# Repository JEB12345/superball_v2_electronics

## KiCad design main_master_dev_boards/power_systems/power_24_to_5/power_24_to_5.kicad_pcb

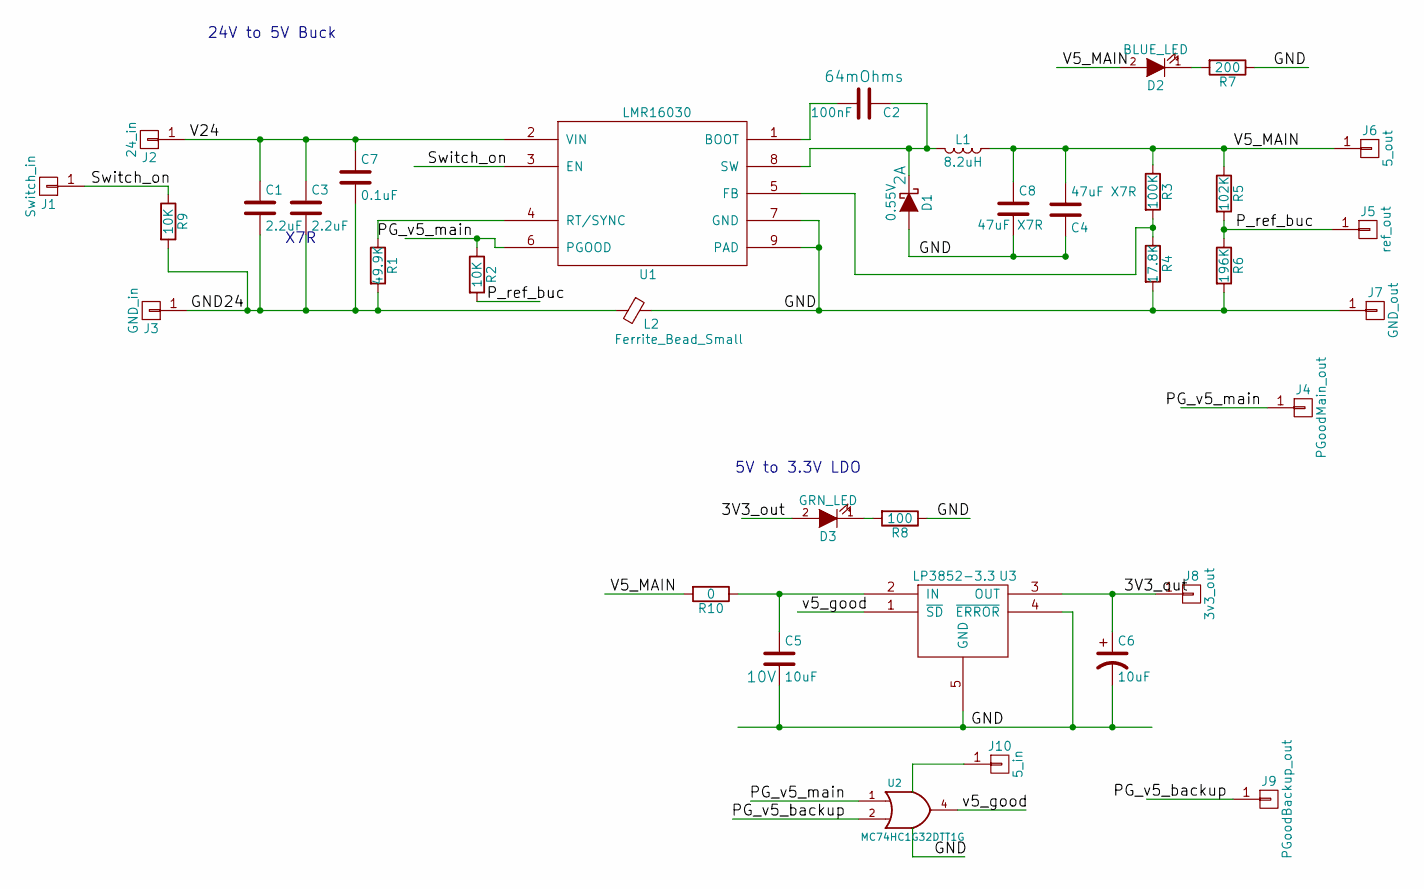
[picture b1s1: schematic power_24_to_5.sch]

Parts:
C1, C3: 2.2uF; C_0805_HandSoldering
C2: 100nF; C_0805_HandSoldering
C4, C8: 47uF X7R; C_2220_HandSoldering
C5: 10uF; C_0805_HandSoldering; Voltage 10V
C6: 10uF; C_0805_HandSoldering
C7: 0.1uF; C_0805_HandSoldering
D1: 0.55V; D_SOD-123
D2: BLUE_LED; LED_0603
D3: GRN_LED; LED_0603
J1: Switch_in; pinhead-01x01_3x1
J2: 24_in; pinhead-01x01_3x1
J3: GND_in; pinhead-01x01_3x1_square
J4: PGoodMain_out; pinhead-01x01_3x1
J5: ref_out; pinhead-01x01_3x1
J6: 5_out; pinhead-01x01_3x1
J7: GND_out; pinhead-01x01_3x1_square
J8: 3v3_out; pinhead-01x01_3x1
J9: PGoodBackup_out; pinhead-01x01_3x1
J10: 5_in; pinhead-01x01_3x1
L1: 8.2uH; Bourns-SRP7028A
L2: Ferrite_Bead_Small; C_0805_HandSoldering
R1: 49.9K; R_0805_HandSoldering
R2, R9: 10K; R_0805_HandSoldering
R3: 100K; R_0805_HandSoldering
R4: 17.8K; R_0805_HandSoldering
R5: 102K; R_0805_HandSoldering
R6: 196K; R_0805_HandSoldering
R7: 200; R_0805_HandSoldering
R8: 100; R_0805_HandSoldering
R10: 0; R_0603
U1: LMR16030; HSOIC-8-1EP_Pitch1.27mm_noVias
U2: MC74HC1G32DTT1G; SOT-23-5_HandSoldering
U3: LP3852-3.3; SOT-223

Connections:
/3V3_out: C6.1, D3.2 (A), J8.1, U3.3 (OUT)
/GND24: C1.2, C3.2, C7.2, J3.1, L2.2, R1.2, R9.2
/PG_v5_backup: J9.1, U2.2
/PG_v5_main: J4.1, R2.1, U1.6 (PGOOD), U2.1
/P_ref_buc: J5.1, R2.2, R5.2, R6.1
/Switch_on: J1.1, R9.1, U1.3 (EN)
/V5_MAIN: C4.2, C8.1, D2.2 (A), J6.1, L1.1, R3.1, R5.1, R10.2
/V24: C1.1, C3.1, C7.1, J2.1, U1.2 (VIN)
/v5_good: U2.4, U3.1 (~SD)
GND: C4.1, C5.2, C6.2, C8.2, D1.2 (A), J7.1, L2.1, R4.2, R6.2, R7.1, R8.1, U1.7 (GND), U1.9 (PAD), U2.3 (GND), U3.4 (~ERROR), U3.5 (GND)
unnamed: C2.1, D1.1 (K), L1.2, U1.8 (SW)
unnamed: C2.2, U1.1 (BOOT)
unnamed: C5.1, R10.1, U3.2 (IN)
unnamed: D2.1 (K), R7.2
unnamed: D3.1 (K), R8.2
unnamed: R1.1, U1.4 (RT/SYNC)
unnamed: R3.2, R4.1, U1.5 (FB)
VCC: J10.1, U2.5 (VCC)

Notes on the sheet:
24V to 5V Buck
5V to 3.3V LDO
X7R

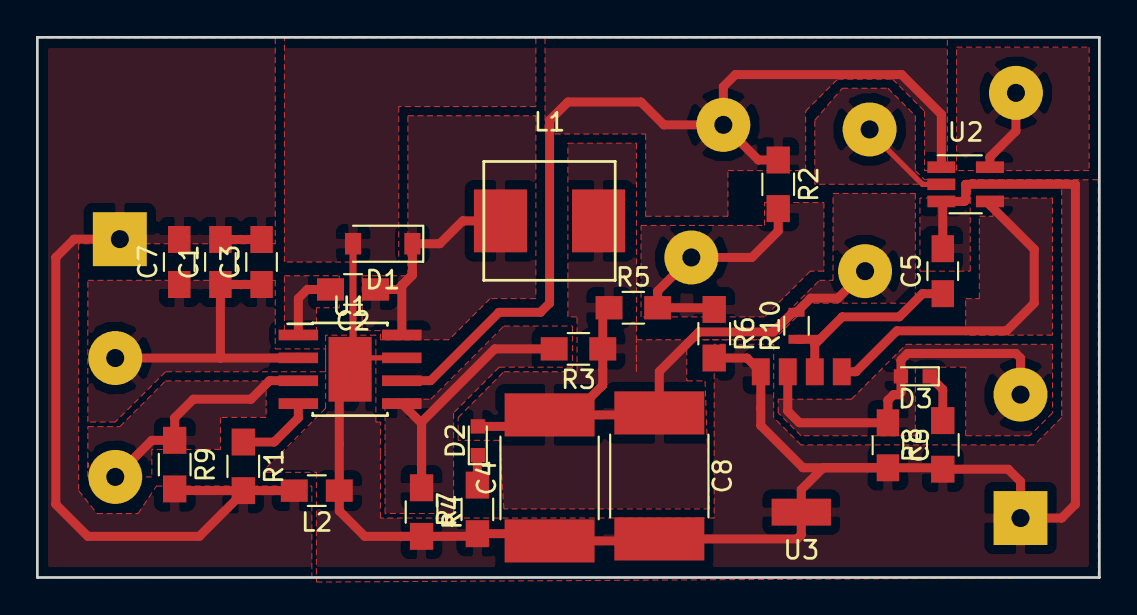
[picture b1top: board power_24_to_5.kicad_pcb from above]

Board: 2 copper layers, 59.0 x 30.0 mm, 36 parts (0 on the bottom side), 18 nets.

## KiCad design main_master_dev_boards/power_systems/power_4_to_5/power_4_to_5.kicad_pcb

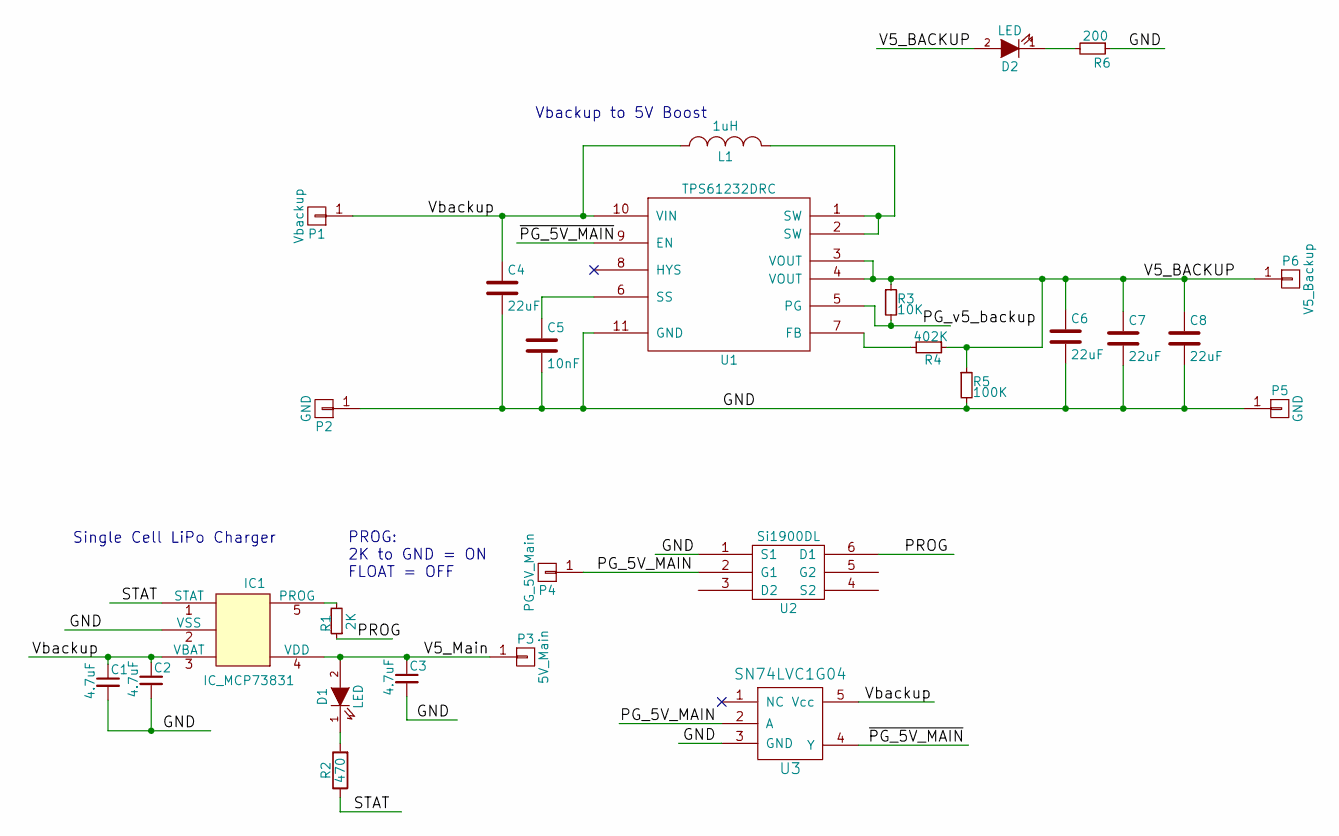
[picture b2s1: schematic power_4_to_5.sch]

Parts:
C1, C2, C3: 4.7uF; C_0805_HandSoldering
C4, C6, C7, C8: 22uF; C_0805_HandSoldering
C5: 10nF; C_0805_HandSoldering
D1, D2: LED; LED_0805
IC1: IC_MCP73831; dp_devices-SOT-23-5
L1: 1uH; XFL4020
P1: Vbackup; pinhead-01x01_3x1
P2, P5: GND; pinhead-01x01_3x1_square
P3: 5V_Main; pinhead-01x01_3x1
P4: PG_5V_Main; pinhead-01x01_3x1
P6: V5_Backup; pinhead-01x01_3x1
R1: 2K; R_0805_HandSoldering
R2: 470; R_0805_HandSoldering
R3: 10K; R_0805_HandSoldering
R4: 402K; R_0805_HandSoldering
R5: 100K; R_0805_HandSoldering
R6: 200; R_0805_HandSoldering
U1: TPS61232DRC; DFN-10-1EP_3x3mm_Pitch0.5mm
U2: Si1900DL; SOT323-6
U3: SN74LVC1G04; SOT-23-5_HandSoldering

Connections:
/GND: C1.2, C2.2, C3.2, C4.2, C5.2, C6.2, C7.2, C8.2, IC1.2 (VSS), P2.1, P5.1, R5.2, R6.1, U1.11 (GND), U2.1 (S1), U3.3 (GND)
/PG_5V_MAIN: P4.1, U2.2 (G1), U3.2 (A)
/PG_v5_backup: R3.2, U1.5 (PG)
/PROG: R1.1, U2.6 (D1)
/STAT: IC1.1 (STAT), R2.1
/V5_BACKUP: C6.1, C7.1, C8.1, D2.2 (A), P6.1, R3.1, R4.1, R5.1, U1.3 (VOUT), U1.4 (VOUT)
/V5_Main: C3.1, D1.2 (A), IC1.4 (VDD), P3.1
/Vbackup: C1.1, C2.1, C4.1, IC1.3 (VBAT), L1.1, P1.1, U1.10 (VIN), U3.5 (Vcc)
/~PG_5V_MAIN: U1.9 (EN), U3.4 (Y)
unnamed: C5.1, U1.6 (SS)
unnamed: D1.1 (K), R2.2
unnamed: D2.1 (K), R6.2
unnamed: IC1.5 (PROG), R1.2
unnamed: L1.2, U1.1 (SW), U1.2 (SW)
unnamed: R4.2, U1.7 (FB)

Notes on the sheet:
Single Cell LiPo Charger
Vbackup to 5V Boost
PROG: 2K to GND = ON FLOAT = OFF

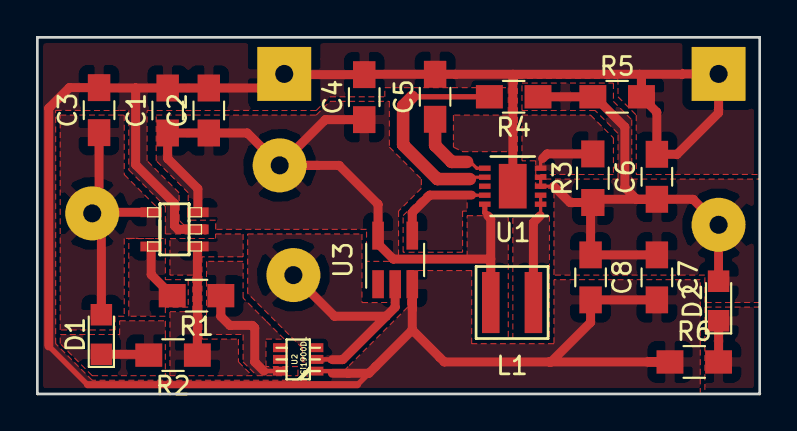
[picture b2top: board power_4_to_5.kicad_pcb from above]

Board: 2 copper layers, 40.1 x 19.8 mm, 27 parts (0 on the bottom side), 15 nets.

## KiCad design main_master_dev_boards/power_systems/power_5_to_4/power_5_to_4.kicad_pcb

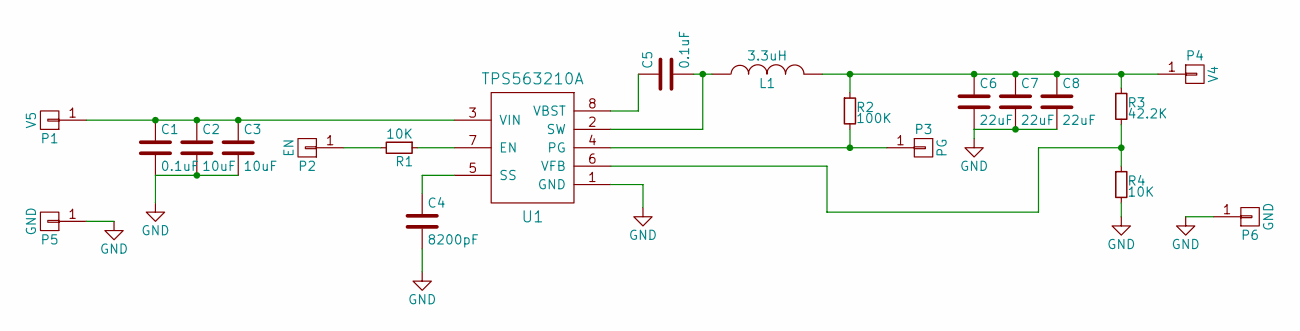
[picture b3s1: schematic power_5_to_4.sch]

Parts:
C1, C5: 0.1uF; C_0805_HandSoldering
C2, C3: 10uF; C_0805_HandSoldering
C4: 8200pF; C_0805_HandSoldering
C6, C7, C8: 22uF; C_0805_HandSoldering
L1: 3.3uH; SRP4020TA
P1: V5; pinhead-01x01_3x1
P2: EN; pinhead-01x01_3x1
P3: PG; pinhead-01x01_3x1
P4: V4; pinhead-01x01_3x1
P5, P6: GND; pinhead-01x01_3x1_square
R1, R4: 10K; R_0805_HandSoldering
R2: 100K; R_0805_HandSoldering
R3: 42.2K; R_0805_HandSoldering
U1: TPS563210A; SOT-23-8_Handsoldering

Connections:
GND: C1.2, C2.2, C3.2, C4.2, C6.2, C7.2, C8.2, P5.1, P6.1, R4.2, U1.1 (GND)
unnamed: C1.1, C2.1, C3.1, P1.1, U1.3 (VIN)
unnamed: C4.1, U1.5 (SS)
unnamed: C5.1, U1.8 (VBST)
unnamed: C5.2, L1.1, U1.2 (SW)
unnamed: C6.1, C7.1, C8.1, L1.2, P4.1, R2.1, R3.1
unnamed: P2.1, R1.2
unnamed: P3.1, R2.2, U1.4 (PG)
unnamed: R1.1, U1.7 (EN)
unnamed: R3.2, R4.1, U1.6 (VFB)

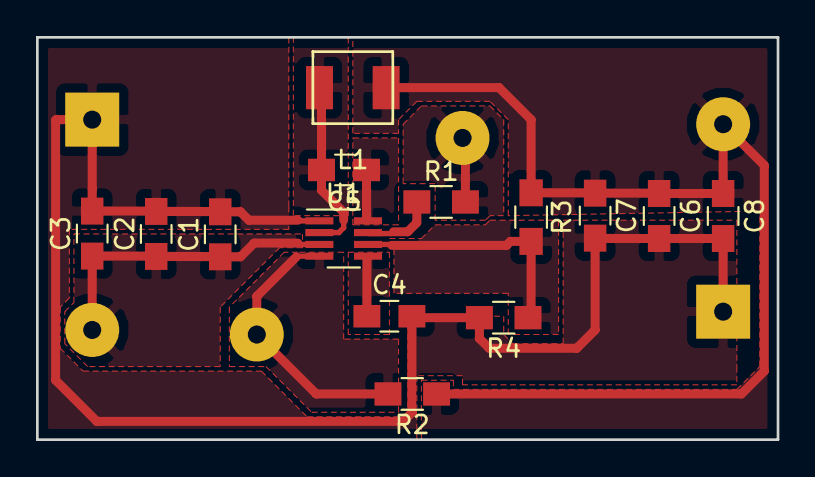
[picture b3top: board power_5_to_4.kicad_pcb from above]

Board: 2 copper layers, 41.1 x 22.4 mm, 20 parts (0 on the bottom side), 10 nets.

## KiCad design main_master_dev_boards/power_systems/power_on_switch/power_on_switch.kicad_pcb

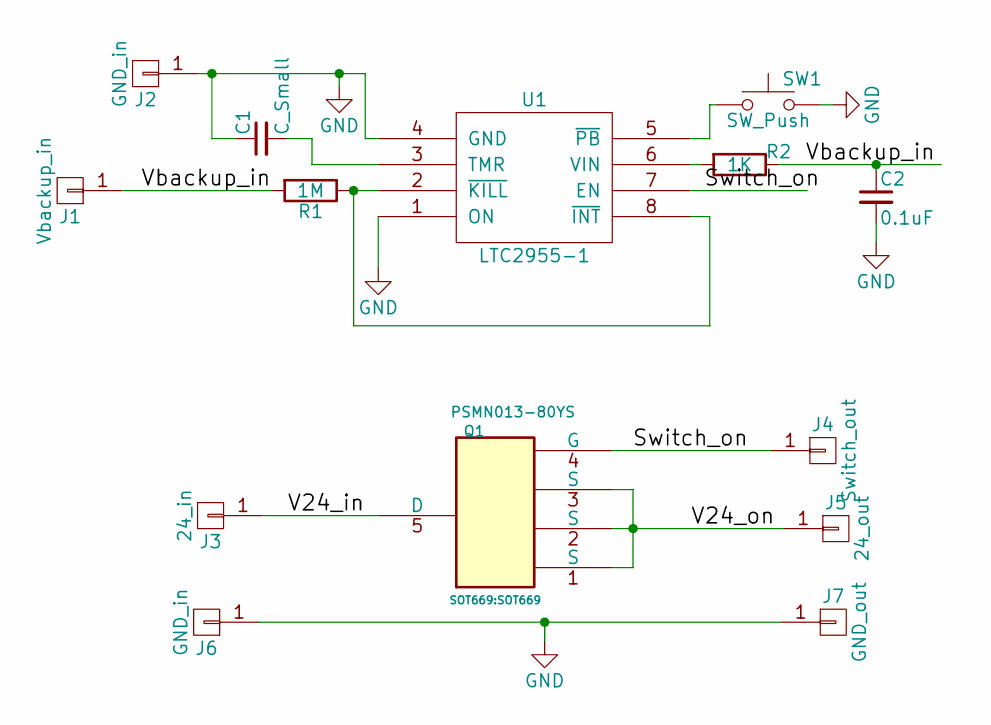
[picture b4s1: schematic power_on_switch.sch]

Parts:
C1: C_Small; C_0805_HandSoldering
C2: 0.1uF; C_0805_HandSoldering
J1: Vbackup_in; pinhead-01x01_3x1
J2, J6: GND_in; pinhead-01x01_3x1_square
J3: 24_in; pinhead-01x01_3x1
J4: Switch_out; pinhead-01x01_3x1
J5: 24_out; pinhead-01x01_3x1
J7: GND_out; pinhead-01x01_3x1_square
Q1: PSMN013-80YS; SOT669
R1: 1M; R_0805_HandSoldering
R2: 1K; R_0805_HandSoldering
SW1: SW_Push; microclasp_2
U1: LTC2955-1; TSOT-23-8

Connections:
/Switch_on: J4.1, Q1.4 (G), U1.7 (EN)
/V24_in: J3.1, Q1.5 (D)
/V24_on: J5.1, Q1.1 (S), Q1.2 (S), Q1.3 (S)
/Vbackup_in: C2.1, J1.1, R1.2, R2.1
GND: C1.1, C2.2, J2.1, J6.1, J7.1, SW1.2, U1.1 (ON), U1.4 (GND)
unnamed: C1.2, U1.3 (TMR)
unnamed: R1.1, U1.2 (~KILL), U1.8 (~INT)
unnamed: R2.2, U1.6 (VIN)
unnamed: SW1.1, U1.5 (~PB)

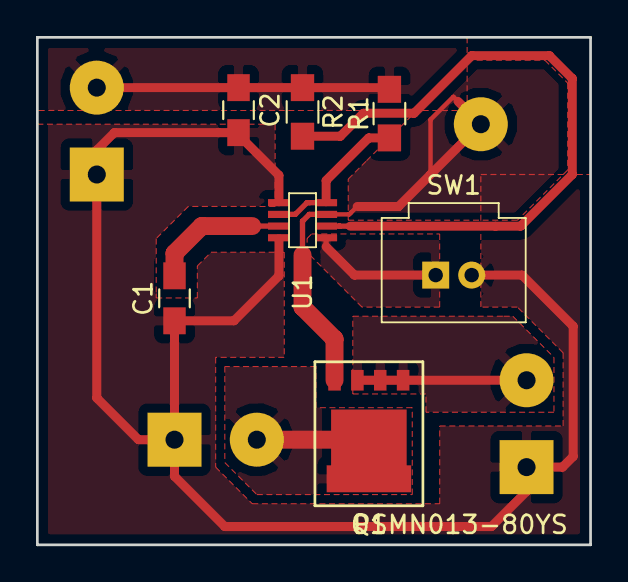
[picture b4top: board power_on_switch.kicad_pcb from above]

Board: 2 copper layers, 30.7 x 28.2 mm, 14 parts (0 on the bottom side), 9 nets.

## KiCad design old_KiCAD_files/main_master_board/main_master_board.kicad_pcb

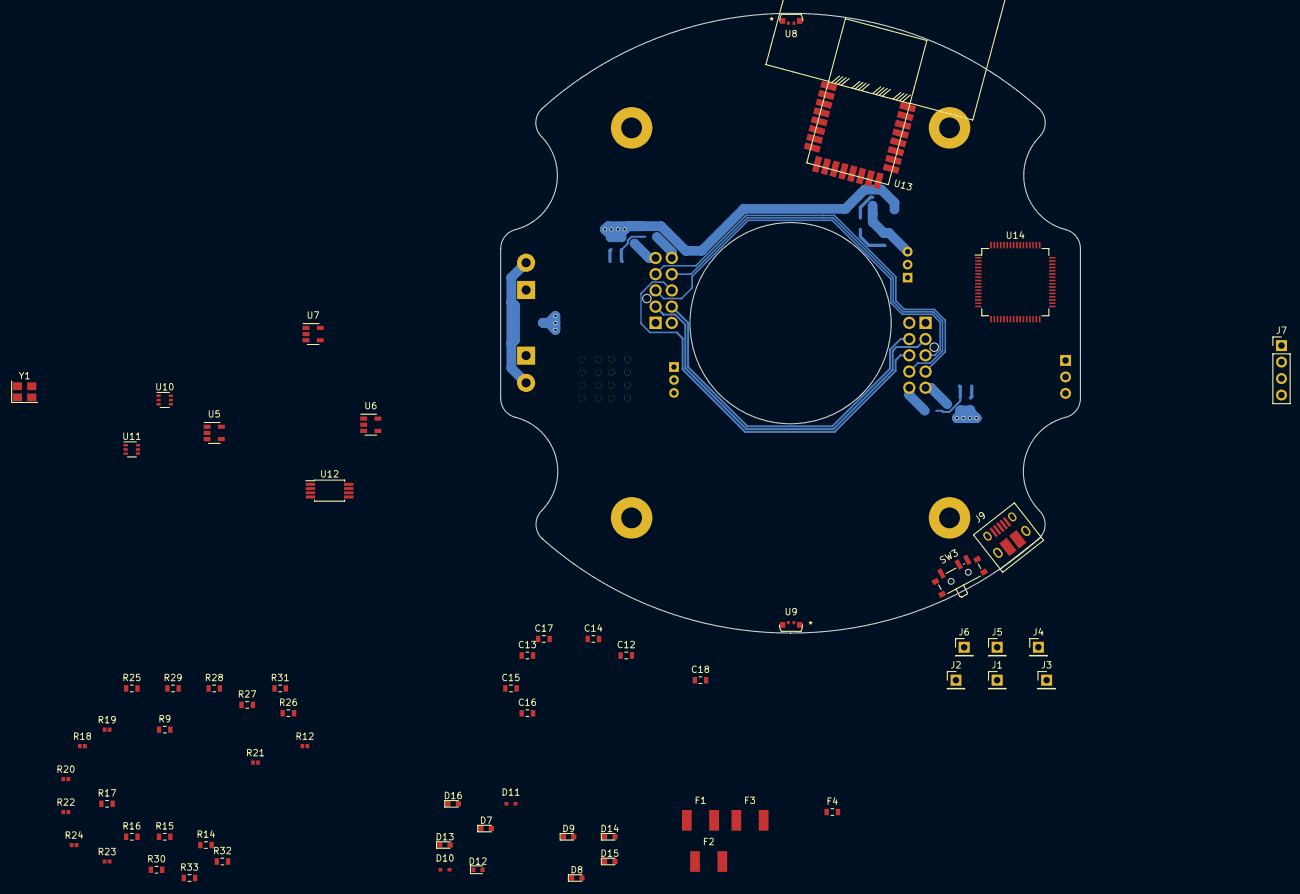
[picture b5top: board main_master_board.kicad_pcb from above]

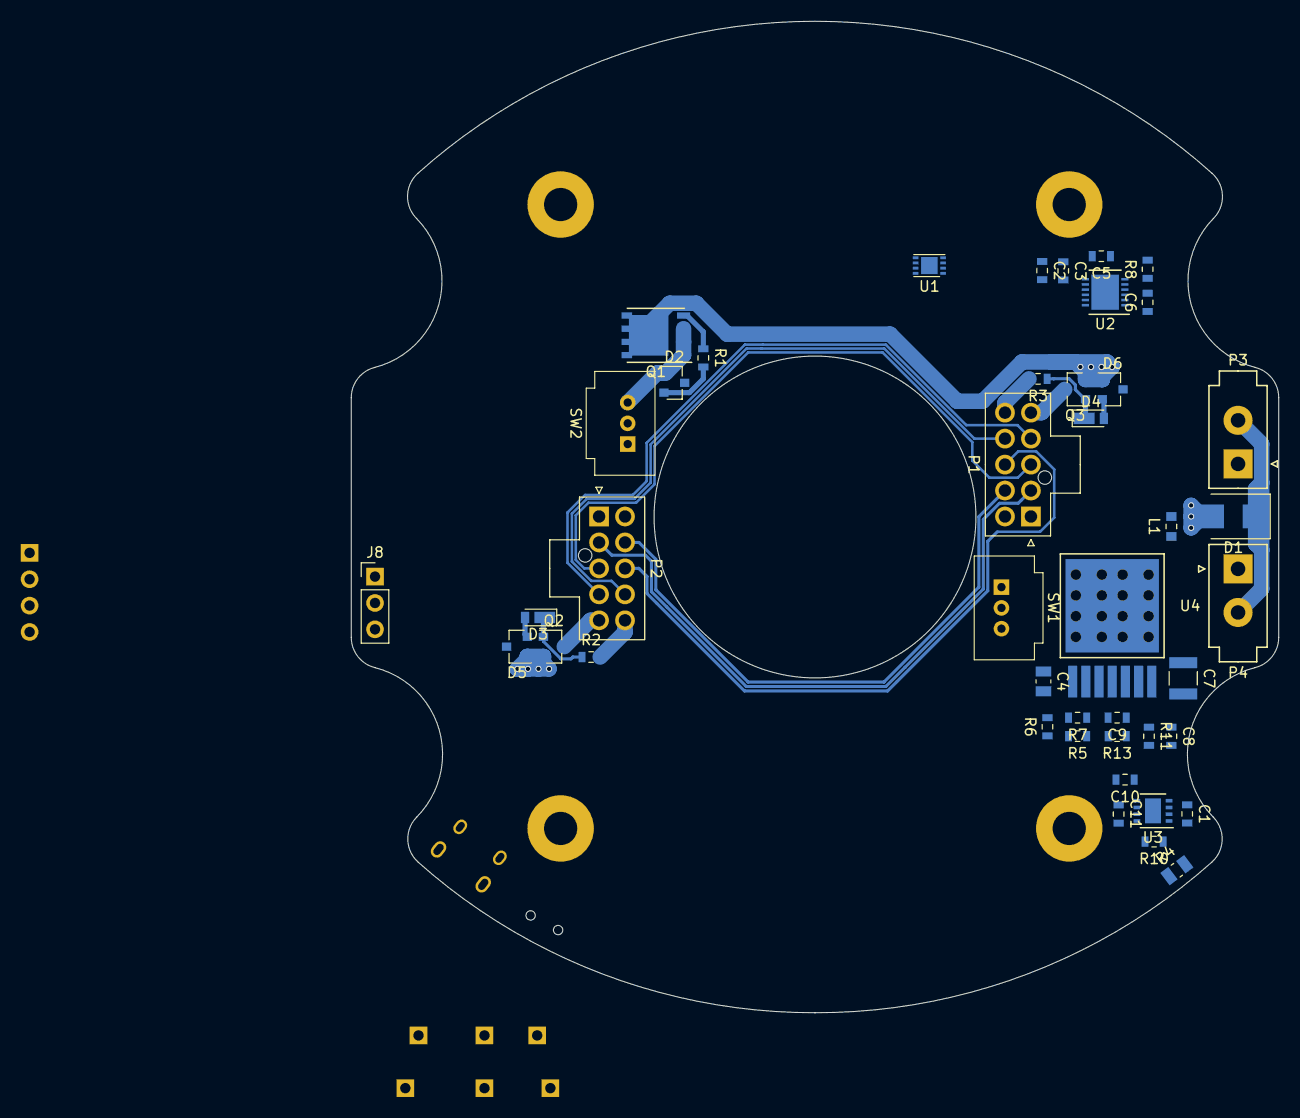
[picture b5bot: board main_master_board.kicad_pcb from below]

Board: 4 copper layers, 89.3 x 95.5 mm, 110 parts (43 on the bottom side), 85 nets.

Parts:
C1, C11: 4.7uF; C_0603_1608Metric
C2, C6, C14: 10uF; C_0603_1608Metric
C3, C15: 2.2uF; C_0603_1608Metric
C4: 10uF; C_0805_2012Metric
C5: 10pF; C_0603_1608Metric
C7: 100uF; C_1210_3225Metric
C8: 0.022uF; C_0603_1608Metric
C9: 4700pF; C_0603_1608Metric
C10: 10nF; C_0603_1608Metric
C12, C13, C16, C17, C18: 0.1uF; C_0603_1608Metric
D1: P6SMB30AT3G; D_SMB
D2, D5, D6: 15V; SOT-23
D3, D4: RF05VAM2STR; D_TUMD2
D7: GRN_LED; LED_0603
D8: ORG_LED; LED_0603
D9: Red LED; LED_0603
D10: uClamp0511P; SLP1006P2
D11: uClamp3311P; SLP1006P2
D12: ESD5Z2.5T1G; D_SOD-523
D13: uC_status; LED_0603
D14, D15, D16: LED; LED_0603
F1: MF-MSMF200-2; SMD-1812
F2, F3: MF-MSMF150-2; SMD-1812
F4: 500mA; R_0603_1608Metric
J1, J2, J3, J4, J5, J6: Conn_01x01; Pin_Header_Straight_1x01_Pitch2.54mm
J7: Conn_01x04_Male; Pin_Header_Straight_1x04_Pitch2.54mm
J8: Conn_01x03_Male; Pin_Header_Straight_1x03_Pitch2.54mm
J9: USB_OTG; USB_Micro-B_10103594-0001LF
L1: 2.0A/0.05 DCR; R_0603_1608Metric_Pad0.84x1.00mm_HandSolder
P1, P2: CONN_02X05; Molex_NanoFit_2x05x2.50mm_Straight
P3: Hebi_1; Molex_MiniFit-JR-5556-02A_2x01x4.20mm_Straight
P4: Hebi_2; Molex_MiniFit-JR-5556-02A_2x01x4.20mm_Straight
P5, P6, P7, P8: Mounting Holes; MountingHole_3.2mm_M3_Pad
Q1: Si7461DP; SO-8_PowerPAK_Vishay_Single
Q2, Q3: Q_PMOS_GSD; SOT-23
R1, R2, R3, R5: 10k; R_0603_1608Metric
R4: 0; R_0805_2012Metric
R6: 178k; R_0603_1608Metric
R7, R10, R25: 100k; R_0603_1608Metric
R8: 66.5k; R_0603_1608Metric
R9, R14: 680; R_0603_1608Metric
R11: 34k; R_0603_1608Metric
R12: 680; R_0402_1005Metric
R13: 6.49k; R_0603_1608Metric
R15, R16, R17: 0.02; R_0603_1608Metric
R18, R19, R22: 470; R_0402_1005Metric
R20, R21, R23, R24: 200; R_0402_1005Metric
R26: 27k; R_0603_1608Metric
R27: 400; R_0603_1608Metric
R28: 50; R_0603_1608Metric
R29, R30, R33: 470; R_0603_1608Metric
R31, R32: 33; R_0603_1608Metric
SW1, SW2: SW_SPDT; microclasp_3
SW3: SW_SPDT; SW_SPDT_PCM12
U1: ADG5419; LFCSP-8-1EP_2x3mm_P0.5mm
U2: LT3083-DFN; DFN-12-1EP_4x4mm_Pitch0.5mm
U3: AS1364; DFN-8-1EP_3x3mm_Pitch0.65mm
U4: LMZ14203H; TO-PMOD
U5, U6, U7: INA197; SOT-23-5
U8, U9: RGB_LED; APFA2507QBDSEEZGKC
U10, U11: Si1900DL; SOT-363_SC-70-6
U12: TPS2111; TSSOP-8_4.4x3mm_P0.65mm
U13: DWM1000; dmw1000
U14: MKL26Z64VLH4; LQFP-64_10x10mm_Pitch0.5mm
Y1: 16MHz; Crystal_SMD_Abracon_ABM8G-4pin_3.2x2.5mm

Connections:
+3V3: C13.2, D13.2, SW3.1, U8.2, U9.2, U12.6, U13.5, U13.6, U13.7
+24V: C4.2, D1.1, P3.2, P4.2, R6.2, R7.2, U1.1, U4.1
/Power_conversion/3V3: D7.2, D11.2, J3.1, R16.1, U5.3, U7.3, U7.5
/Power_conversion/3V3_FUSE: F2.2, R16.2, U7.4
/Power_conversion/3V3_cur: J6.1, U7.1
/Power_conversion/3V3_out: C6.1, F2.1, U2.1, U2.2, U2.3, U2.4, U2.5, U2.13
/Power_conversion/4V: D12.2, J2.1, R17.1, U6.3, U6.5
/Power_conversion/4V_EN: R4.1, U3.2
/Power_conversion/4V_FUSE: F3.2, R17.2, U6.4
/Power_conversion/4V_cur: J5.1, U6.1
/Power_conversion/4V_out: C10.1, C11.1, F3.1, R10.2, U3.5, U3.6
/Power_conversion/V5: C1.1, C2.1, C3.1, D9.2, D10.2, R4.2, R15.1, U2.7, U2.8, U2.9, U2.10, U2.12, U3.3, U3.4, U5.5
/Power_conversion/V5_FUSE: F1.2, R15.2, U5.4
/Power_conversion/V5_out: C7.2, C8.1, F1.1, R11.1, U4.7
/V24_in_batt: D6.1, Q1.5, Q3.2, SW1.3, U1.2, U1.4
/V24_in_batt_raw: P1.5, P1.6, Q3.3
/V24_in_ext: D2.1, D5.1, Q1.1, Q1.2, Q1.3, Q2.2, SW2.3, U1.6, U1.8
/V24_in_ext_raw: P2.5, P2.6, Q2.3
/signal_1s: P1.2, P2.2
/signal_2s: P1.7, P2.7
/signal_3s: P1.3, P2.3
/signal_4s: P1.8, P2.8
/signal_5s: P1.4, P2.4
/signal_6s: P1.9, P2.9
/uC_and_Sensors/DWM_CLK: U13.20, U14.58
/uC_and_Sensors/DWM_CS: U13.17, U14.49
/uC_and_Sensors/DWM_IRQ: U13.22, U14.29
/uC_and_Sensors/DWM_MISO: U13.19, U14.52
/uC_and_Sensors/DWM_MOSI: U13.18, U14.51
/uC_and_Sensors/LED/T13: D16.2, U14.50
/uC_and_Sensors/RESET: J8.1, SW3.2, U13.3, U14.28, U14.34
/uC_and_Sensors/RGB_B_led: R21.1, R24.1, U10.6
/uC_and_Sensors/RGB_G_led: R20.1, R23.1, U11.3
/uC_and_Sensors/RGB_R_led: R19.1, R22.1, U11.6
/uC_and_Sensors/RXXLED: R29.2, U13.13
/uC_and_Sensors/SWD_CLK: J8.3, U14.22
/uC_and_Sensors/SWD_DIO: J8.2, U14.25
/uC_and_Sensors/TXLED: R30.2, U13.12
/uC_and_Sensors/VUSB: C12.1, R25.1, U12.8
/uC_and_Sensors/V_uC: C14.1, C16.1, C17.1, F4.2, R28.1, U12.7, U14.8
/uC_and_Sensors/WAKEUP: U13.2, U14.27
/uC_and_Sensors/rgb_b: J7.3, U10.2, U14.20
/uC_and_Sensors/rgb_g: J7.2, U11.5, U14.21
/uC_and_Sensors/rgb_r: J7.1, U11.2, U14.19
/uC_and_Sensors/uC_status: J7.4, U10.5, U14.17
GND: C1.2, C2.2, C3.2, C4.1, C5.2, C6.2, C7.1, C9.2, C11.2, C12.2, C13.1, C14.2, C15.1, C16.2, C17.2, C18.1, D10.1, D11.1, D12.1, D14.1, D15.1, J9.5, J9.6, L1.1, P5.1, P6.1, R5.1, R8.2, R9.1, R12.1, R13.2, R14.1, R26.2, R27.2, R28.2, R33.2, SW1.1, SW2.1, SW3.3, U1.3, U1.7, U3.8, U3.9, U4.4, U4.8, U5.2, U6.2, U7.2, U10.1, U10.4, U11.1, U11.4, U12.2, U12.5, U13.8, U13.16, U13.21, U13.23, U13.24, U14.4, U14.15, U14.16, U14.31, U14.47, Y1.2, Y1.4
GNDPWR: D1.2, L1.2, P1.1, P1.10, P2.1, P2.10, P3.1, P4.1, R2.2, R3.2
unnamed: C5.1, R8.1, U2.6
unnamed: C8.2, R11.2, R13.1, U4.6
unnamed: C9.1, U4.5
unnamed: C10.2, U3.7
unnamed: C15.2, F4.1, J9.1
unnamed: D2.2, R1.2
unnamed: D3.1, Q2.1, R2.1
unnamed: D3.2, D5.2
unnamed: D4.1, Q3.1, R3.1
unnamed: D4.2, D6.2
unnamed: D7.1, R9.2
unnamed: D8.1, R12.2
unnamed: D9.1, R14.2
unnamed: D13.1, R18.2
unnamed: D14.2, R29.1
unnamed: D15.2, R30.1
unnamed: D16.1, R33.1
unnamed: J9.2, R32.2
unnamed: J9.3, R31.1
unnamed: Q1.4, R1.1, SW2.2
unnamed: R5.2, R6.1, U4.3
unnamed: R7.1, U4.2
unnamed: R10.1, U3.1
unnamed: R18.1, U10.3
unnamed: R19.2, U9.1
unnamed: R20.2, U9.4
unnamed: R21.2, U9.3
unnamed: R22.2, U8.1
unnamed: R23.2, U8.4
unnamed: R24.2, U8.3
unnamed: R25.2, R26.1, U12.3
unnamed: R27.1, U12.4
unnamed: R31.2, U14.5
unnamed: R32.1, U14.6
unnamed: SW1.2, U1.5
unnamed: U14.3, U14.30, U14.48
unnamed: U14.32, Y1.1
unnamed: U14.33, Y1.3

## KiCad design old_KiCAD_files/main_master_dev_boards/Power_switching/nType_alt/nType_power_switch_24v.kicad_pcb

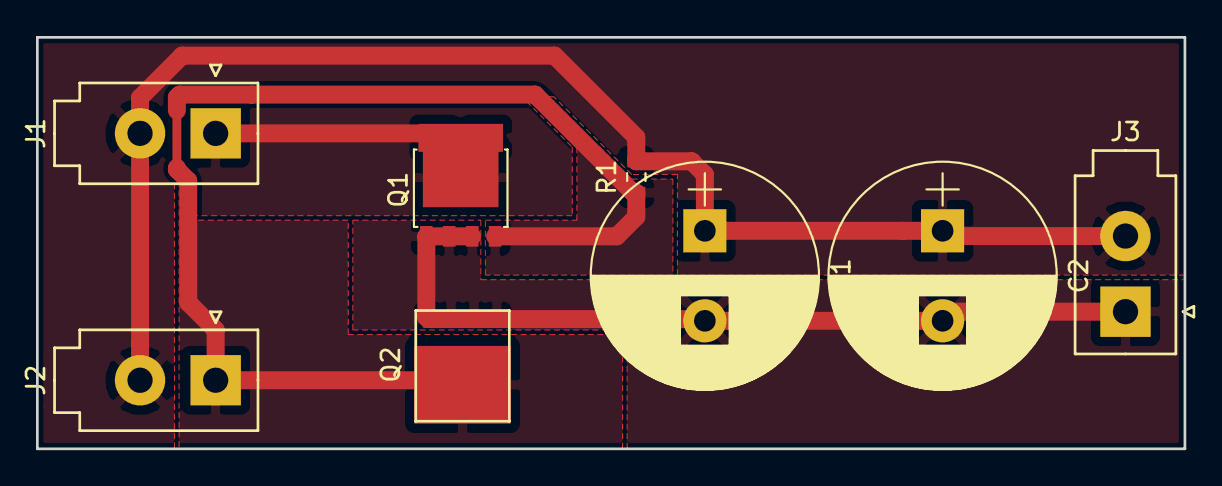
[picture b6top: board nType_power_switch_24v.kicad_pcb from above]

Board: 2 copper layers, 63.8 x 22.9 mm, 8 parts (0 on the bottom side), 4 nets.

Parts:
C1, C2: 1mF; CP_Radial_D12.5mm_P5.00mm
J1: Batt_In; Molex_MiniFit-JR-5556-02A_2x01x4.20mm_Straight
J2: Ext_In; Molex_MiniFit-JR-5556-02A_2x01x4.20mm_Straight
J3: 24_Out; Molex_MiniFit-JR-5556-02A_2x01x4.20mm_Straight
Q1: PSMN013-80YS; SOT-669_LFPAK
Q2: STPS30MxxxDJF; PowerFLAT
R1: 100K; R_0603_1608Metric

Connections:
/24_Out+: C1.1, C2.1, J1.2, J2.2, J3.2, R1.2
/24_Out_GND: C1.2, C2.2, J3.1, Q1.1, Q1.2, Q1.3, Q2.1, Q2.2, Q2.3, Q2.4
/Batt_GND: J1.1, Q1.5
/Ext_GND: J2.1, Q1.4, Q2.5, R1.1

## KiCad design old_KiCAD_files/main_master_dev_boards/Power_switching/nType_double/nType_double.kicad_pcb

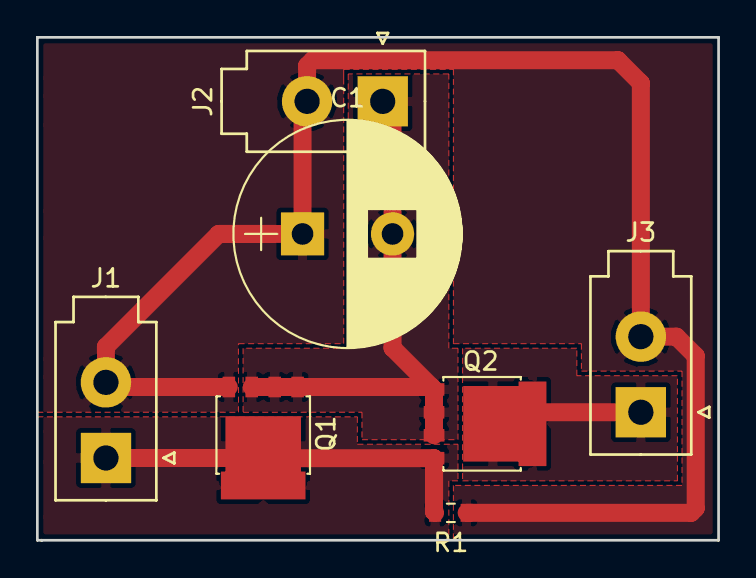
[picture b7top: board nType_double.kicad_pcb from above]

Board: 2 copper layers, 37.8 x 27.9 mm, 7 parts (0 on the bottom side), 4 nets.

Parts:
C1: CP1_Small; CP_Radial_D12.5mm_P5.00mm
J1: Ext_in; Molex_MiniFit-JR-5556-02A_2x01x4.20mm_Straight
J2: Out; Molex_MiniFit-JR-5556-02A_2x01x4.20mm_Straight
J3: Batt_in; Molex_MiniFit-JR-5556-02A_2x01x4.20mm_Straight
Q1, Q2: PSMN013-80YS; SOT-669_LFPAK
R1: R; R_0603_1608Metric

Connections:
/Batt_GND: J3.1, Q2.5
/Ext_GND: J1.1, Q1.5, Q2.4, R1.2
/GND: C1.2, J2.1, Q1.1, Q1.2, Q1.3, Q2.1, Q2.2, Q2.3
/Power: C1.1, J1.2, J2.2, J3.2, Q1.4, R1.1
